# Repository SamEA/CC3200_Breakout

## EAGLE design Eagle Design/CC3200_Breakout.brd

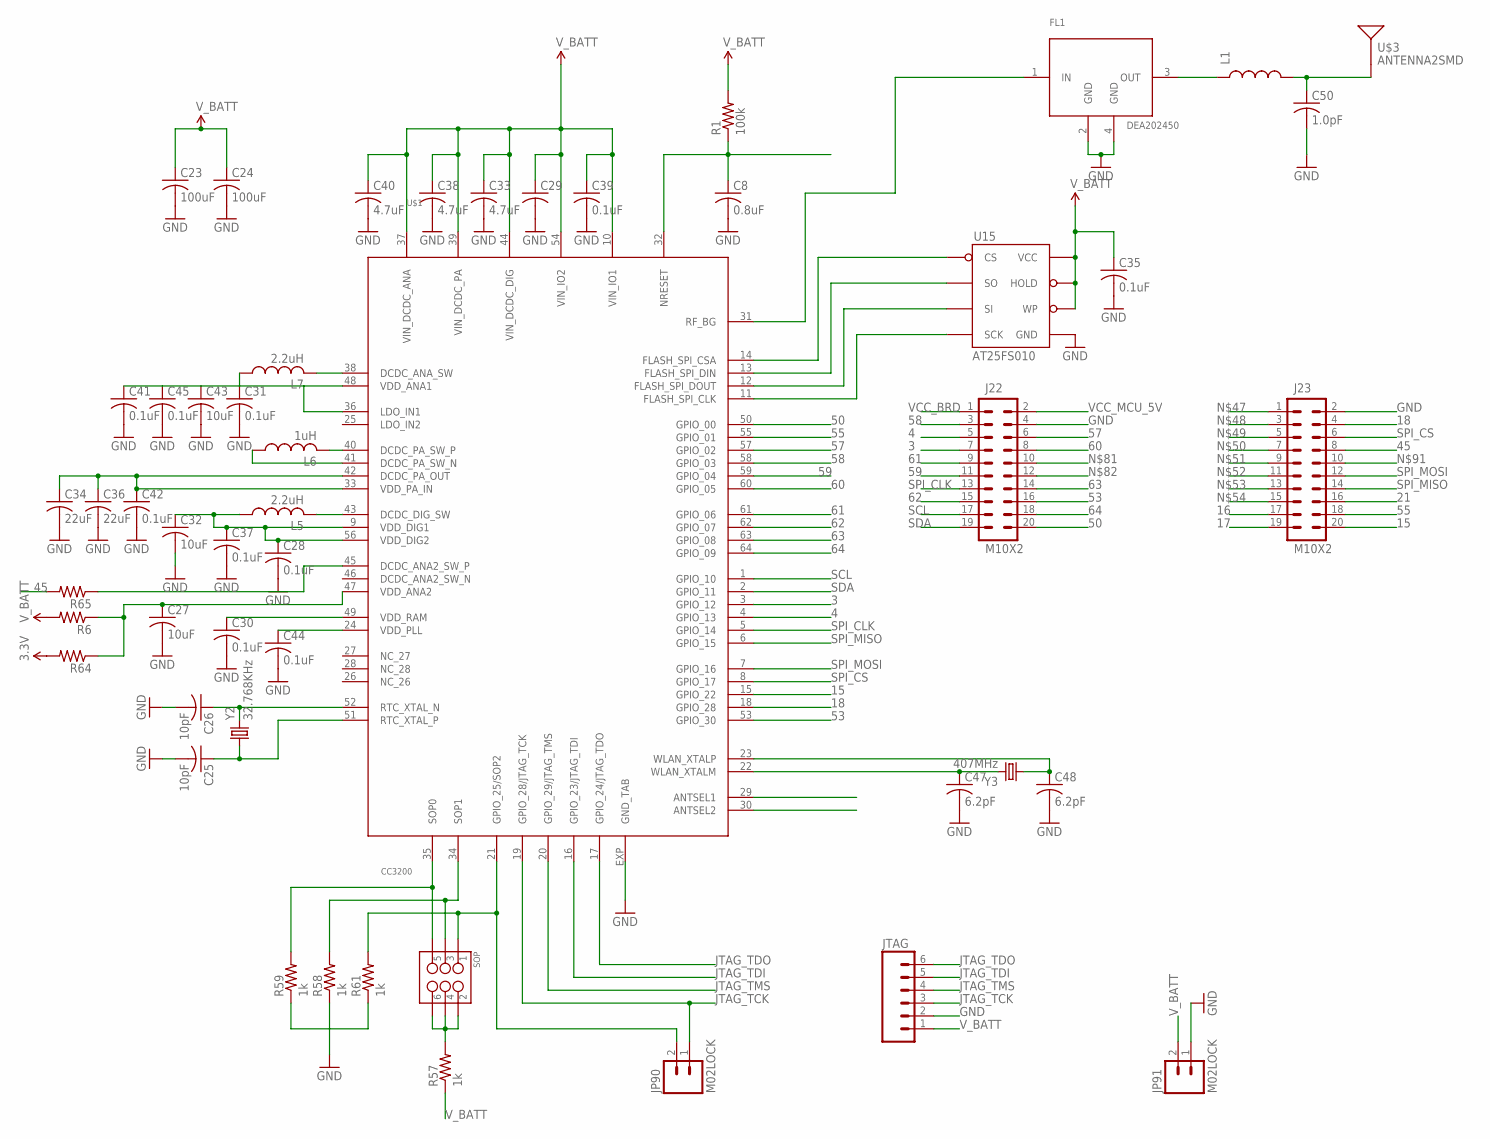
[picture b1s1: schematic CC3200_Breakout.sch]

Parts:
C8: 0.8uF; C0402K
C23, C24: 100uF; C0402K
C25, C26: 10pF; C0402K
C27, C32, C43: 10uF; C0402K
C28, C30, C31, C35, C37, C39, C41, C42, C44, C45: 0.1uF; C0402K
C29: C-USC0402K; C0402K
C33, C38, C40: 4.7uF; C0402K
C34, C36: 22uF; C0402K
C47, C48: 6.2pF; C0402K
C50: 1.0pF; C0402K
FL1: DEA202450
J22, J23: M10X2; 2X10
JP90, JP91: M02LOCK; 1X02_LOCK
JTAG: M06SILK_FEMALE_PTH; 1X06
L1: INDUCTOR-SPARKFUN0402; C0402
L5, L7: 2.2uH; L2012C
L6: 1uH; L2012C
R1: 100k; R0402
R6, R64, R65: R-US_R0402; R0402
R57, R58, R59, R61: 1k; R0402
SOP: M03X22X3_SILK_MALE_PTH; 2X3
U15: AT25FS010; SO08WIDE
U$1: CC3200; PVQFN-N64
U$3: ANTENNA2SMD; ANTENNA-CHIP2
Y2: 32.768KHz; CRYSTAL-SMD-5X3
Y3: 407MHz; CRYSTAL-SMD-5X3

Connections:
3: J22.7, U$1.3 (GPIO_12)
3.3V: R64.2
4: J22.5, U$1.4 (GPIO_13)
15: J23.20, U$1.15 (GPIO_22)
16: J23.17
17: J23.19
18: J23.4, U$1.18 (GPIO_28)
21: J23.16
45: J23.8, R65.2
50: J22.20, U$1.50 (GPIO_00)
53: J22.16, U$1.53 (GPIO_30)
55: J23.18, U$1.55 (GPIO_01)
57: J22.6, U$1.57 (GPIO_02)
58: J22.3, U$1.58 (GPIO_03)
59: J22.11, U$1.59 (GPIO_04)
60: J22.8, U$1.60 (GPIO_05)
61: J22.9, U$1.61 (GPIO_06)
62: J22.15, U$1.62 (GPIO_07)
63: J22.14, U$1.63 (GPIO_08)
64: J22.18, U$1.64 (GPIO_09)
GND: C8.2, C23.2, C24.2, C25.2, C26.2, C27.2, C28.2, C29.2, C30.2, C31.2, C32.2, C33.2, C34.2, C35.2, C36.2, C37.2, C38.2, C39.2, C40.2, C41.2, C42.2, C43.2, C44.2, C45.2, C47.2, C48.2, C50.1, C50.2, FL1.2 (GND), FL1.4 (GND), J22.4, J23.2, JP91.1, JTAG.2, L1.2, R58.1, R59.1, R61.1, U15.4 (GND), U$1.EXP (GND_TAB), U$3.FEED
JTAG_TCK: JP90.1, JTAG.3, U$1.19 (GPIO_28/JTAG_TCK)
JTAG_TDI: JTAG.5, U$1.16 (GPIO_23/JTAG_TDI)
JTAG_TDO: JTAG.6, U$1.17 (GPIO_24/JTAG_TDO)
JTAG_TMS: JTAG.4, U$1.20 (GPIO_29/JTAG_TMS)
unnamed: C26.1, U$1.52 (RTC_XTAL_N), Y2.3 (2)
unnamed: C25.1, U$1.51 (RTC_XTAL_P), Y2.1
unnamed: C31.1, C41.1, C43.1, C45.1, L7.1, U$1.36 (LDO_IN1), U$1.48 (VDD_ANA1)
unnamed: L7.2, U$1.38 (DCDC_ANA_SW)
unnamed: R57.2, SOP.2, SOP.4, SOP.6
unnamed: L6.2, U$1.40 (DCDC_PA_SW_P)
unnamed: L6.1, U$1.41 (DCDC_PA_SW_N)
unnamed: FL1.1 (IN), U$1.31 (RF_BG)
unnamed: C34.1, C36.1, C42.1, U$1.33 (VDD_PA_IN), U$1.42 (DCDC_PA_OUT)
unnamed: L5.2, U$1.43 (DCDC_DIG_SW)
unnamed: R65.1, U$1.45 (DCDC_ANA2_SW_P)
unnamed: R59.2, SOP.5, U$1.35 (SOP0)
unnamed: C8.1, R1.1, U$1.32 (NRESET)
unnamed: C28.1, C32.1, C37.1, L5.1, U$1.9 (VDD_DIG1), U$1.56 (VDD_DIG2)
unnamed: C30.1, U$1.49 (VDD_RAM)
unnamed: C44.1, U$1.24 (VDD_PLL)
unnamed: C27.1, R6.1, R64.1, U$1.47 (VDD_ANA2)
unnamed: R58.2, SOP.3, U$1.34 (SOP1)
unnamed: JP90.2, R61.2, SOP.1, U$1.21 (GPIO_25/SOP2)
unnamed: C47.1, U$1.22 (WLAN_XTALM), Y3.3 (2)
unnamed: C48.1, U$1.23 (WLAN_XTALP), Y3.1
unnamed: U15.1 (CS), U$1.14 (FLASH_SPI_CSA)
unnamed: U15.2 (SO), U$1.13 (FLASH_SPI_DIN)
unnamed: U15.5 (SI), U$1.12 (FLASH_SPI_DOUT)
unnamed: U15.6 (SCK), U$1.11 (FLASH_SPI_CLK)
unnamed: FL1.3 (OUT), L1.1
SCL: J22.17, U$1.1 (GPIO_10)
SDA: J22.19, U$1.2 (GPIO_11)
SPI_CLK: J22.13, U$1.5 (GPIO_14)
SPI_CS: J23.6, U$1.8 (GPIO_17)
SPI_MISO: J23.14, U$1.6 (GPIO_15)
SPI_MOSI: J23.12, U$1.7 (GPIO_16)
VCC_BRD: J22.1
VCC_MCU_5V: J22.2
V_BATT: C23.1, C24.1, C29.1, C33.1, C35.1, C38.1, C39.1, C40.1, JP91.2, JTAG.1, R1.2, R6.2, R57.1, U15.3 (WP), U15.7 (HOLD), U15.8 (VCC), U$1.10 (VIN_IO1), U$1.37 (VIN_DCDC_ANA), U$1.39 (VIN_DCDC_PA), U$1.44 (VIN_DCDC_DIG), U$1.54 (VIN_IO2)

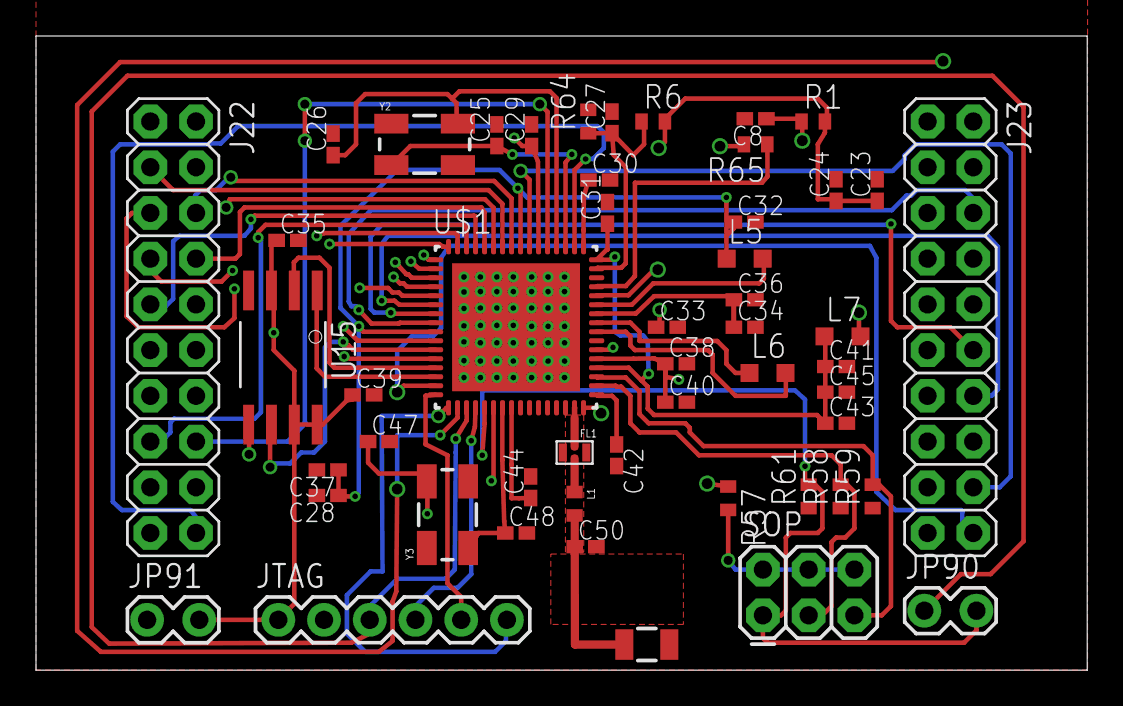
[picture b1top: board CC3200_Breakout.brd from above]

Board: 4 copper layers, 58.4 x 35.2 mm, 51 parts (0 on the bottom side), 54 nets.

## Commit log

2014-06-26 Added Images
2014-12-03 update schematic
2014-12-05 BRD and name
    Rename the component on schema to match name with LaunchPad XL and added
    first BRD file with component placement only
2014-12-06 Some placement and renaming
    Removed Pull up and Pull down from Flash Chip and rename SPI pins
2014-12-06 Modified connectors
2014-12-06 Some modification at the connectors
2014-12-06 Added JTAG and Lock Connectors
2014-12-06 Locked Connectors
2014-12-07 SOP
    Added SOP connector and addition connector JP90 to be use as jumper wire
    used in Energia
2014-12-10 Routing
    Add connector for Battery JP91
    Start Routing
    Added design rule for and Gerber of smart-prototyping.
2014-12-12 4 Layers and routing
    Made PCB 4 Layers and more routing, plus vias under mcu
2014-12-12 update brd
    update brd
2014-12-16 Routing
    Almost finished routing except Anttena
2014-12-16 Update png
2014-12-17 Antenna
2014-12-17 Anttena

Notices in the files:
parts and their libraries:
SparkFun-DigitalIC: Licensing: CC v3.0 Share-Alike You are welcome to use this library for commercial purposes.
